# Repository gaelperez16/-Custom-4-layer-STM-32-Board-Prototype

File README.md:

# -Custom-4-layer-STM-32-Board-Prototype

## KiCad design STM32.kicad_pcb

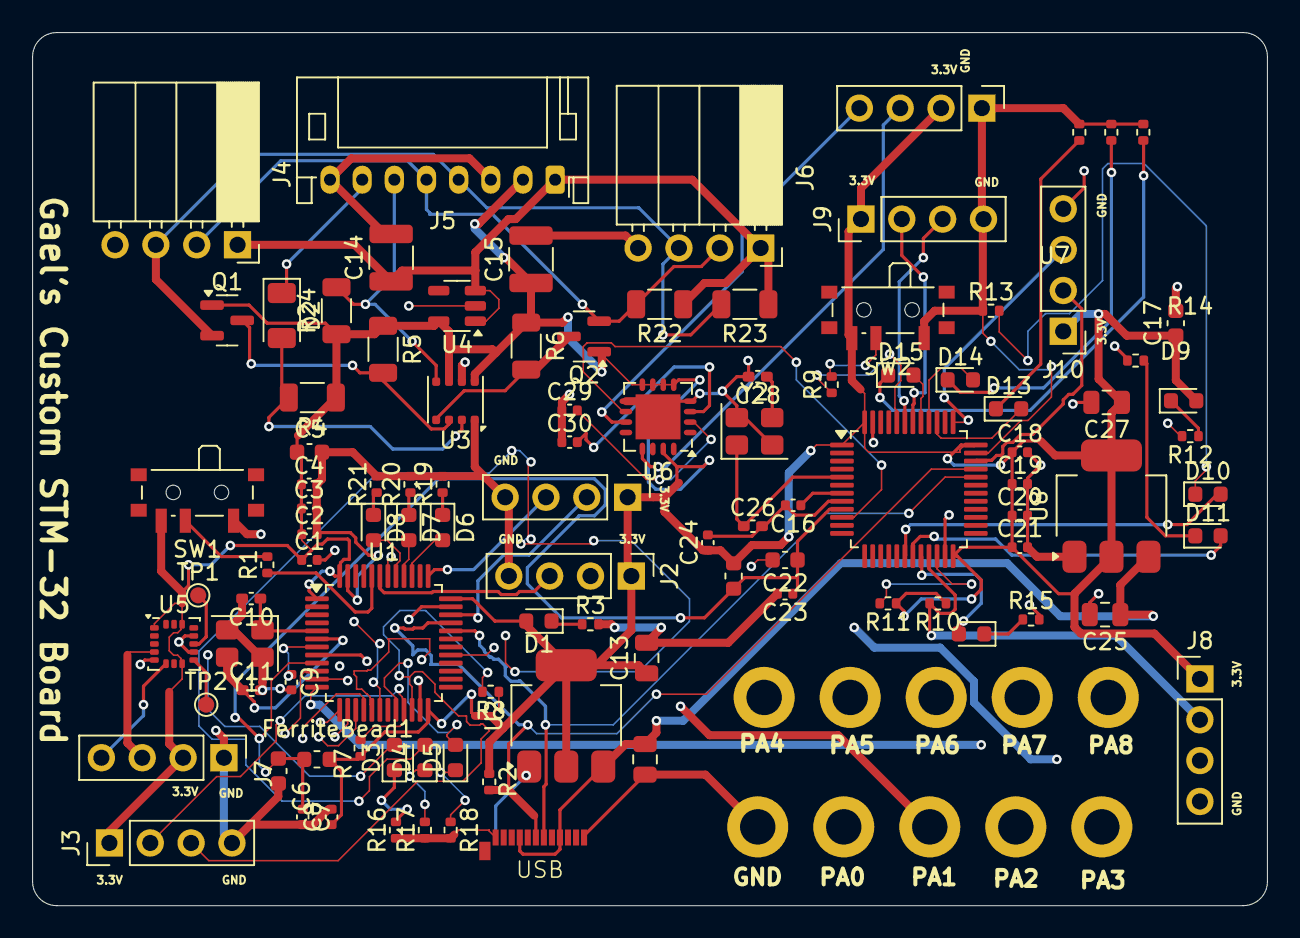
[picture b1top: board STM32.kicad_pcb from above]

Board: 4 copper layers, 76.8 x 54.3 mm, 112 parts (0 on the bottom side), 80 nets.

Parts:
AS3935_4pinmale1: Conn_01x04; PinHeader_1x04_P2.54mm_Vertical
C1, C2, C3, C4, C9, C16, C18, C19, C20, C21, C29, C30: 100n; C_0402_1005Metric
C5, C17: 10u; C_0603_1608Metric
C6, C22: 10n; C_0603_1608Metric
C7, C8, C23, C24: 1u; C_0402_1005Metric
C10, C11, C26, C28: 10p; C_0402_1005Metric_Pad0.74x0.62mm_HandSolder
C12, C13, C25, C27: 22u; C_0805_2012Metric
C14, C15: 10u; C_1210_3225Metric
D1, D3, D4, D5, D6, D7, D8, D9, D10, D11, D12, D13, D14, D15: RED; LED_0603_1608Metric
D2: IN4007; D_1206_3216Metric
FerriteBead1, FerriteBead2: 120R; L_0603_1608Metric
H1, H2, H3, H4, H5, H6, H7, H8, H9, H10: MountingHole_Pad; MountingHole_2.2mm_M2_DIN965_Pad
J1, J2, J3, J8, J9, J10: Conn_01x04_Pin; PinHeader_1x04_P2.54mm_Vertical
J4: Conn_01x04_Pin; PinSocket_1x04_P2.54mm_Horizontal
J5: Conn_01x08_Pin; JST_PH_S8B-PH-K_1x08_P2.00mm_Horizontal
J6: Conn_01x04_Socket; PinSocket_1x04_P2.54mm_Horizontal
J7: Conn_01x04; PinHeader_1x04_P2.54mm_Vertical
P2: USB_C_Plug; USB_C_Plug_Molex_105444
Q1, Q2: 2N7002; SOT-23
R1, R9: 10k; R_0402_1005Metric
R2: 1K5; R_0402_1005Metric
R3, R7, R8, R10, R11, R12, R13, R14, R15, R16, R17, R18, R19, R20, R21, R25, R26, R27: 1k5; R_0402_1005Metric
R4, R5, R6, R22, R23, R24: 10K; R_1206_3216Metric
SW1, SW2: SW_SPDT; SW_SPDT_PCM12
TP1, TP2: TestPoint; TestPoint_Pad_D1.0mm
U1, U7: STM32F103C8T6; LQFP-48_7x7mm_P0.5mm
U2, U8: AMS1117-3.3; SOT-223-3_TabPin2
U3: BME680; Bosch_LGA-8_3x3mm_P0.8mm_ClockwisePinNumbering
U4: MIC5219-3.3YM5; SOT-23-5
U5: LIS3DH; LGA-16_3x3mm_P0.5mm_LayoutBorder3x5y
U6: AS3935; MLPQ-16-1EP_4x4mm_P0.65mm_EP2.8x2.8mm
Y1, Y2: 16MHz; Crystal_SMD_3225-4Pin_3.2x2.5mm

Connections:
+3.3V: AS3935_4pinmale1.2, C1.1, C2.1, C3.1, C4.1, C5.1, C8.1, C13.1, C15.1, C17.1, C18.1, C19.1, C20.1, C21.1, C24.1, C27.1, D1.2 (A), D9.2 (A), FerriteBead1.2, FerriteBead2.2, J1.1, J2.1, J3.1, J5.2, J7.2, J8.1, J9.1, J10.1, Q1.1 (G), Q2.1 (G), R2.1, R4.1, R5.1, R6.1, R7.1, R8.1, R10.1, R11.1, R24.1, SW1.3 (C), SW2.3 (C), U1.1 (VBAT), U1.24 (VDD), U1.36 (VDD), U1.48 (VDD), U2.2 (VO), U3.6 (VDDIO), U3.8 (VDD), U4.5 (OUT), U5.1 (VDD_IO), U5.8 (CS), U5.14 (VDD), U6.5 (Vdd), U6.6 (VReg), U6.7 (EN), U6.8 (CS), U6.15 (AD0), U7.1 (VBAT), U7.24 (VDD), U7.36 (VDD), U7.48 (VDD), U8.2 (VO)
+3.3V Analog: C6.1, C7.1, C22.1, C23.1, FerriteBead1.1, FerriteBead2.1, U1.9 (VDDA), U7.9 (VDDA)
/Adafruit BME680/CS: D2.1 (K), J5.7
/Adafruit BME680/CS_3V: D2.2 (A), R4.2, U3.2 (CSB)
/Adafruit BME680/SCK/SCL: J4.2, J5.5, J6.2, Q2.2 (S), R22.2
/Adafruit BME680/SCL_3V: Q2.3 (D), R6.2, U3.4 (SCK)
/Adafruit BME680/SDA_3V: Q1.3 (D), R5.2, U3.3 (SDI)
/Adafruit BME680/SDI/SDA: J4.3, J5.4, J6.3, Q1.2 (S), R23.2
/Adafruit BME680/SDO/ADR: J5.6, R24.2, U3.5 (SDO)
/Boot: R1.1, U1.44 (BOOT0)
/I2C2_SCL: J3.2, R7.2, U1.21 (PB10)
/I2C2_SDA: J3.3, R8.2, U1.22 (PB11)
/NetReset: C9.1, U1.7 (NRST)
/PWR_LED_K: D1.1 (K), R3.1
/SWCLK: J1.3, U1.37 (PA14)
/SWDIO: J1.2, U1.34 (PA13)
/Second Processor/Boot: R9.1, U7.44 (BOOT0)
/Second Processor/I2C2_SCL_2nd: J8.2, R10.2, U7.21 (PB10)
/Second Processor/I2C2_SDA_2nd: J8.3, R11.2, U7.22 (PB11)
/Second Processor/NetReset: C16.1, U7.7 (NRST)
/Second Processor/PWR_LED_K: D9.1 (K), R12.1
/Second Processor/SWCLK: J10.3, U7.37 (PA14)
/Second Processor/SWDIO: J10.2, U7.34 (PA13)
/Second Processor/Sw_Boot: R9.2, SW2.2 (B)
/Second Processor/USART1_RX: J9.3, U7.43 (PB7)
/Second Processor/USART1_TX: J9.2, U7.42 (PB6)
/Sw_Boot: R1.2, SW1.2 (B)
/USART1_RX: J2.3, U1.43 (PB7)
/USART1_TX: J2.2, U1.42 (PB6)
GND: AS3935_4pinmale1.1, C1.2, C2.2, C3.2, C4.2, C5.2, C6.2, C7.2, C8.2, C9.2, C10.2, C11.2, C12.2, C13.2, C14.2, C15.2, C16.2, C17.2, C18.2, C19.2, C20.2, C21.2, C22.2, C23.2, C24.2, C25.2, C26.2, C27.2, C28.2, C29.1, C30.1, H1.1, J1.4, J2.4, J3.4, J4.4, J5.3, J5.8, J6.4, J7.1, J8.4, J9.4, J10.4, P2.A1 (GND), P2.A12 (GND), P2.B1 (GND), P2.B12 (GND), R3.2, R12.2, R13.1, R14.1, R15.2, R16.1, R17.1, R18.2, R19.2, R20.2, R21.2, R25.2, R26.2, R27.2, SW1.1 (A), SW2.1 (A), U1.8 (VSSA), U1.23 (VSS), U1.35 (VSS), U1.47 (VSS), U2.1 (GND), U3.1 (GND), U3.7 (GND), U4.2 (GND), U5.5 (GND), U5.10 (GND), U5.12 (GND), U6.4 (GND), U6.9 (SI), U6.16 (AD1), U6.17 (GNDPAD), U7.8 (VSSA), U7.23 (VSS), U7.35 (VSS), U7.47 (VSS), U8.1 (GND), Y1.2, Y1.4, Y2.2, Y2.4
HSE_IN: C10.1, U1.5 (PD0), Y1.1
HSE_IN1: C26.1, U7.5 (PD0), Y2.1
HSE_OUT: C11.1, U1.6 (PD1), Y1.3
HSE_OUT2: C28.1, Y2.3
IRQ: U6.10 (IRQ), U7.10 (PA0)
unnamed: D3.1 (K), R16.2
unnamed: D4.1 (K), R17.2
unnamed: D5.1 (K), R18.1
unnamed: D6.1 (K), R19.1
unnamed: D7.1 (K), R20.1
unnamed: D8.1 (K), R21.1
unnamed: D10.1 (K), R13.2
unnamed: D11.1 (K), R14.2
unnamed: D12.1 (K), R15.1
unnamed: D13.1 (K), R25.1
unnamed: D14.1 (K), R26.1
unnamed: D15.1 (K), R27.1
unnamed: H2.1, U1.10 (PA0)
unnamed: H3.1, U1.11 (PA1)
unnamed: H4.1, U1.12 (PA2)
unnamed: H5.1, U1.13 (PA3)
unnamed: H6.1, U1.14 (PA4)
unnamed: H7.1, U1.15 (PA5)
unnamed: H8.1, U1.16 (PA6)
unnamed: H9.1, U1.17 (PA7)
unnamed: H10.1, U1.29 (PA8)
unnamed: TP1.1, U5.11 (INT1)
unnamed: TP2.1, U5.9 (INT2)
unnamed: C30.2, U6.3 (IN+)
unnamed: C29.2, U6.2 (IN-)
PB0: D3.2 (A), U1.18 (PB0)
PB00: D10.2 (A), U7.18 (PB0)
PB1: D4.2 (A), U1.19 (PB1)
PB2: D5.2 (A), U1.20 (PB2)
PB3: D6.2 (A), U1.39 (PB3)
PB4: D7.2 (A), U1.40 (PB4)
PB5: D8.2 (A), U1.41 (PB5)
PB11: D11.2 (A), U7.19 (PB1)
PB22: D12.2 (A), U7.20 (PB2)
PB33: D13.2 (A), U7.39 (PB3)
PB44: D14.2 (A), U7.40 (PB4)
PB55: D15.2 (A), U7.41 (PB5)
SCL1: J7.3, U5.4 (SCL/SPC)
SCL2: AS3935_4pinmale1.3, U6.13 (MOSI/SDA)
SDA1: J7.4, U5.6 (SDA/SDI/SDO)
SDA2: AS3935_4pinmale1.4, U6.11 (SCL)
USB_D+: P2.A6 (D+), R2.2, U1.33 (PA12), U7.33 (PA12)
USB_D-: P2.A7 (D-), U1.32 (PA11), U7.32 (PA11)
VBUS: C12.1, C25.1, P2.A4 (VBUS), P2.A9 (VBUS), P2.B4 (VBUS), P2.B9 (VBUS), U2.3 (VI), U8.3 (VI)
VCC: C14.1, J4.1, J5.1, J6.1, R22.1, R23.1, U4.1 (IN), U4.3 (EN)
